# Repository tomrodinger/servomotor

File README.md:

# Gearotons M17 — an open-source servomotor you can talk to

The M17 is a NEMA-17 **integrated servomotor**: motor, closed-loop driver, motion controller and
magnetic encoder in one unit. It daisy-chains over RS-485, ships with Python and Arduino libraries,
and has a first-party [MCP server](https://github.com/Gearotons/servomotor-mcp) so an AI assistant
(Claude Desktop, Claude Code, Cursor, …) can drive real motors from plain English.

Hardware, firmware and software are all in this repository under the MIT license.

| | M17-34 | M17-40 | M17-48 | M17-60 |
|---|---|---|---|---|
| Length | 33.5 mm | 40.1 mm | 48.7 mm | 59.7 mm |
| Holding torque | 0.28 N·m | 0.42 N·m | 0.55 N·m | 0.65 N·m |
| Weight | 210 g | 285 g | 360 g | 470 g |

All sizes: 12–24 V, up to ~1.1 A, up to 560 RPM, closed-loop 32 kHz control, RS-485 at 230400 baud,
64-bit unique ID + one-byte alias per motor, standard NEMA-17 mount. Indoor use (IP20).

**Buy one:** [gearotons.com](https://gearotons.com) (from $20; ships worldwide from Shenzhen).
**Documentation:** [9o.at/M17_1.5](https://9o.at/M17_1.5) ·
[Datasheet (PDF)](servomotor_datasheets/datasheet_latest_en.pdf) ·
[Python API](API_documentation/M17_servomotor_Python_API_documentation.md) ·
[Arduino API](API_documentation/M17_servomotor_Arduino_API_documentation.md)

## Quick start (Python)

```bash
pip install servomotor
```

```python
import time, servomotor

servomotor.open_serial_port()                      # prompts for the USB–RS-485 adapter the first time
m = servomotor.M3("X", time_unit="seconds", position_unit="shaft_rotations")
m.enable_mosfets()
m.trapezoid_move(1.0, 1.0)                         # one full turn, in one second
time.sleep(1.1)
m.disable_mosfets()
servomotor.close_serial_port()
```

That is [`python_programs/example_trapezoid_move.py`](python_programs/example_trapezoid_move.py).
Units are yours to choose (degrees, rotations, radians, encoder counts; seconds or milliseconds) —
the library converts. No STEP/DIR timing, no microstep configuration.

## Quick start (Arduino / ESP32)

Install the **Servomotor** library by Gearotons from the Arduino Library Manager, or from
[`Arduino_library/`](Arduino_library/). Wire the board's UART to an RS-485 transceiver, then:

```cpp
#include <Servomotor.h>

void setup() {
  Servomotor motor('X', Serial1);                  // alias 'X'; the port opens on first use
  motor.setPositionUnit(PositionUnit::SHAFT_ROTATIONS);
  motor.setTimeUnit(TimeUnit::SECONDS);
  motor.enableMosfets();
  motor.trapezoidMove(2.0f, 3.0f);                 // two rotations over three seconds
  delay(4000);
  Serial.println(motor.getPosition());             // commanded position; getHallSensorPosition() reads measured position
}
void loop() {}
```

That is a trimmed [`Arduino_library/example_one_move.cpp`](Arduino_library/example_one_move.cpp)
(the full file adds the ESP32 RS-485 pin definitions).

## Quick start (talk to it)

```bash
uvx --from servomotor-mcp servomotor-mcp        # runs with a simulated motor if no hardware is attached
```

Add it to Claude Desktop or run `claude mcp add gearotons-motor -- uvx --from servomotor-mcp servomotor-mcp`,
then ask: *"Find my motors, then move the one on the bench to 90 degrees and tell me where it ended up."*
Details and the full tool list: [Gearotons/servomotor-mcp](https://github.com/Gearotons/servomotor-mcp).

<p align="center"><a href="https://github.com/Gearotons/servomotor-mcp/releases/download/v0.3.1/M17-claude-code-demo.mp4">▶ 50-second video: the real motor and this session side by side</a> (recorded 2026-09-09 on a bench M17).</p>

## What is in this repository

| Folder | Contents |
|---|---|
| [`firmware/`](firmware/) | Motor firmware (STM32G0), plus [`bootloader_STM32G030/`](bootloader_STM32G030/) and [`bootloader_STM32G031/`](bootloader_STM32G031/) |
| [`PCB/`](PCB/) | Schematics, board layouts and 3D (STEP) models of the controller board |
| [`python_programs/`](python_programs/) | The `servomotor` Python library source, examples, test and characterisation scripts |
| [`Arduino_library/`](Arduino_library/) | The Arduino/ESP32 C++ library and examples |
| [`API_documentation/`](API_documentation/) | Generated Python and Arduino API references (Markdown and PDF) |
| [`servomotor_datasheets/`](servomotor_datasheets/) | Datasheet sources and PDFs (EN, DE, ES, FR, IT, PT), dimension drawings |
| [`production_test_system/`](production_test_system/), [`motor_tests/`](motor_tests/) | How we test motors before they ship |
| [`marketting_page/`](marketting_page/) | Source of the gearotons.com product page |

The command set is data-driven: every firmware command is defined once in
[`motor_commands.json`](python_programs/servomotor/motor_commands.json) and the Python library, the Arduino library and the MCP server are generated
from it, so they always agree.

## Firmware 0.17.0.0

This M17 release adds **Set immediate position target (49)** and
**Set immediate position target and get position (50)**. The second command
returns the latest stored Hall position. Both require an empty motion queue
and enabled closed-loop position control. PID readback (48) remains available.

```python
m.set_immediate_position_target(1000)
measured = m.set_immediate_position_target_and_get_position(2000)
```

Updated bindings are published as [Python 0.13.0](https://pypi.org/project/servomotor/0.13.0/)
and [Arduino 0.11.0](https://github.com/tomrodinger/Servomotor_Arduino_Library/releases/tag/v0.11.0).
See the [client-library release handoff](LIBRARY_RELEASE_HANDOFF.md) for validation,
release receipts and remaining indexing/publishing follow-ups. The release image targets
**M17 hardware 1.5, software compatibility code 3**. Version 0.17.0.0 promotes
the validated 0.17.0.6 implementation; only the development-version byte changes.
See the [release notes](firmware/firmware_releases/servomotor_M17_fw0.17.0.0_scc3_hw1.5.release_notes.txt)
for behavior, client compatibility, upgrade/rollback commands and validation.
The exact stable image passed 35,148+ canary updates with zero communication
errors; see [release-image results](firmware/immediate_target_validation/2026-11-11/release_0.17.0.0/hardware/HARDWARE_RESULTS.txt).
The [firmware release index](firmware/firmware_releases/README.md) lists images,
release notes, checksums and manifests, including the preceding 0.16.0.0 release.

## Immediate targets and ServoTune

Both commands require an empty queue and enabled closed-loop position control.
They retain PID history and protections. Validation runs with interrupts enabled;
only the target/planner stores are masked. Command 50 reads cached Hall position
atomically afterwards, without a sensor recalculation or control-tick wait.
Its reply confirms reference installation, not shaft arrival.

The exact 0.17.0.0 image passed 35,148+ canary updates, both CRC modes,
protection/recovery, native C++ clients and timed-move followups, with zero
communication errors. [Release-image results](firmware/immediate_target_validation/2026-11-11/release_0.17.0.0/hardware/HARDWARE_RESULTS.txt) include timing limits.
Updated Python/Arduino bindings and ServoTune recognize stable 0.17.0.0;
ServoTune also retains the legacy 24-byte reply for development 0.17.0.2.

Try the [ServoTune browser bench](servotune/README.md) without a motor:

```sh
python3 servotune/serve.py
```

The launcher opens a clearly labelled demo with simulated data. The modified
client serializes request/reply transactions and supports both new commands.
The published stable firmware is 0.17.0.0. The preceding 0.16.0.0 release
does not implement immediate-target commands.

## Where the M17 is not the right tool

Direct-drive torque tops out at 0.65 N·m (gear it or go up a frame size for more), it is IP20 and
indoor-only, and it is not a STEP/DIR drop-in for an existing 3D-printer board — it wants a serial
bus and a host that sends it moves. We would rather you know that before you buy.

## Community and support

Questions and builds: [GitHub Discussions](https://github.com/tomrodinger/servomotor/discussions) ·
email [info@gearotons.com](mailto:info@gearotons.com). Issues and pull requests welcome — the whole
stack is here to be read, modified and improved.

Built and assembled by Gearotons in Shenzhen. MIT license — see [LICENSE](LICENSE).

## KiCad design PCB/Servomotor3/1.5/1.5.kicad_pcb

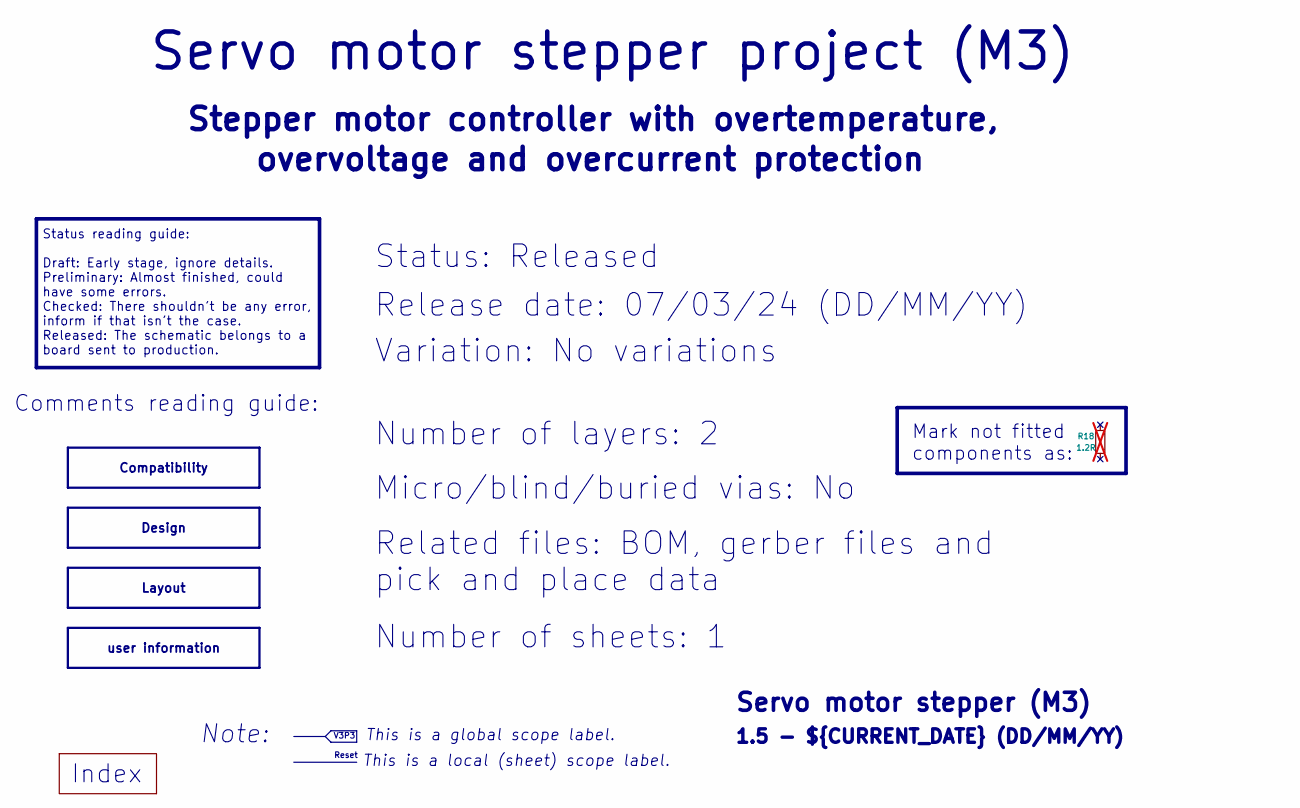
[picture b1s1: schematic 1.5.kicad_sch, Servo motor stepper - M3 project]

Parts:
R18: 1.2R; R_0402_1005Metric; not fitted

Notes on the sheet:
Variation: No variations
${REVISION} - ${CURRENT_DATE} (DD/MM/YY)
Status reading guide: Draft: Early stage, ignore details. Preliminary: Almost finished, could have some errors. Checked: There shouldn't be any error, inform if that isn't the case. Released: The schematic belongs to a board sent to production.
Servo motor stepper project (M3)
This is a global scope label.
Micro/blind/buried vias: No
Status: Released
Comments reading guide:
overvoltage and overcurrent protection
Reset
Note:
Stepper motor controller with overtemperature,
Related files: BOM, gerber files and pick and place data
Number of sheets: 1
This is a local (sheet) scope label.
Index
Mark not fitted components as:
Number of layers: 2
Release date: 07/03/24 (DD/MM/YY)
V3P3
Servo motor stepper (M3)
Design
user information
Compatibility
Layout

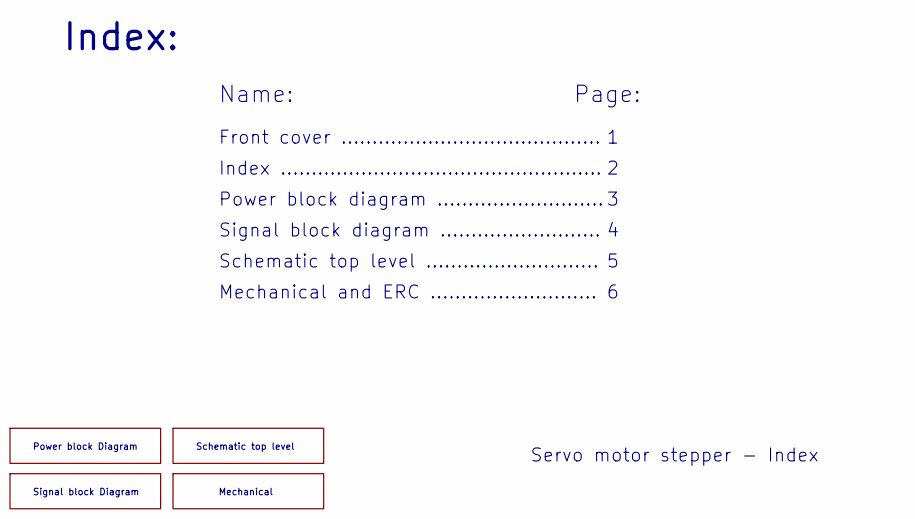
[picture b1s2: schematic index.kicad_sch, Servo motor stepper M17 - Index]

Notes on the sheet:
Power block Diagram
Front cover ..........................................
Mechanical
Schematic top level
Schematic top level ............................
Index ....................................................
Signal block diagram ..........................
Signal block Diagram
Name:
Mechanical and ERC ...........................
Page:
Servo motor stepper - Index
Power block diagram ...........................
Index:

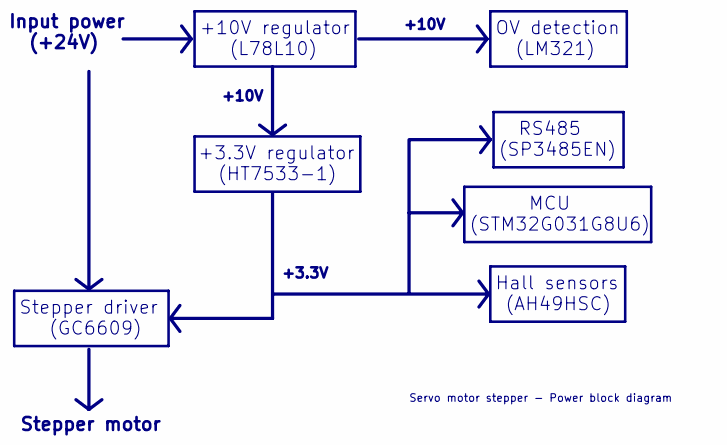
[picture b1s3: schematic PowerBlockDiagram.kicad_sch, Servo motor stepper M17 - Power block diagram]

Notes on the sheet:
+3.3V
Stepper driver (GC6609)
+10V
RS485 (SP3485EN)
Hall sensors (AH49HSC)
Servo motor stepper - Power block diagram
+3.3V regulator (HT7533-1)
+10V regulator (L78L10)
OV detection (LM321)
Input power (+24V)
Stepper motor
MCU (STM32G031G8U6)

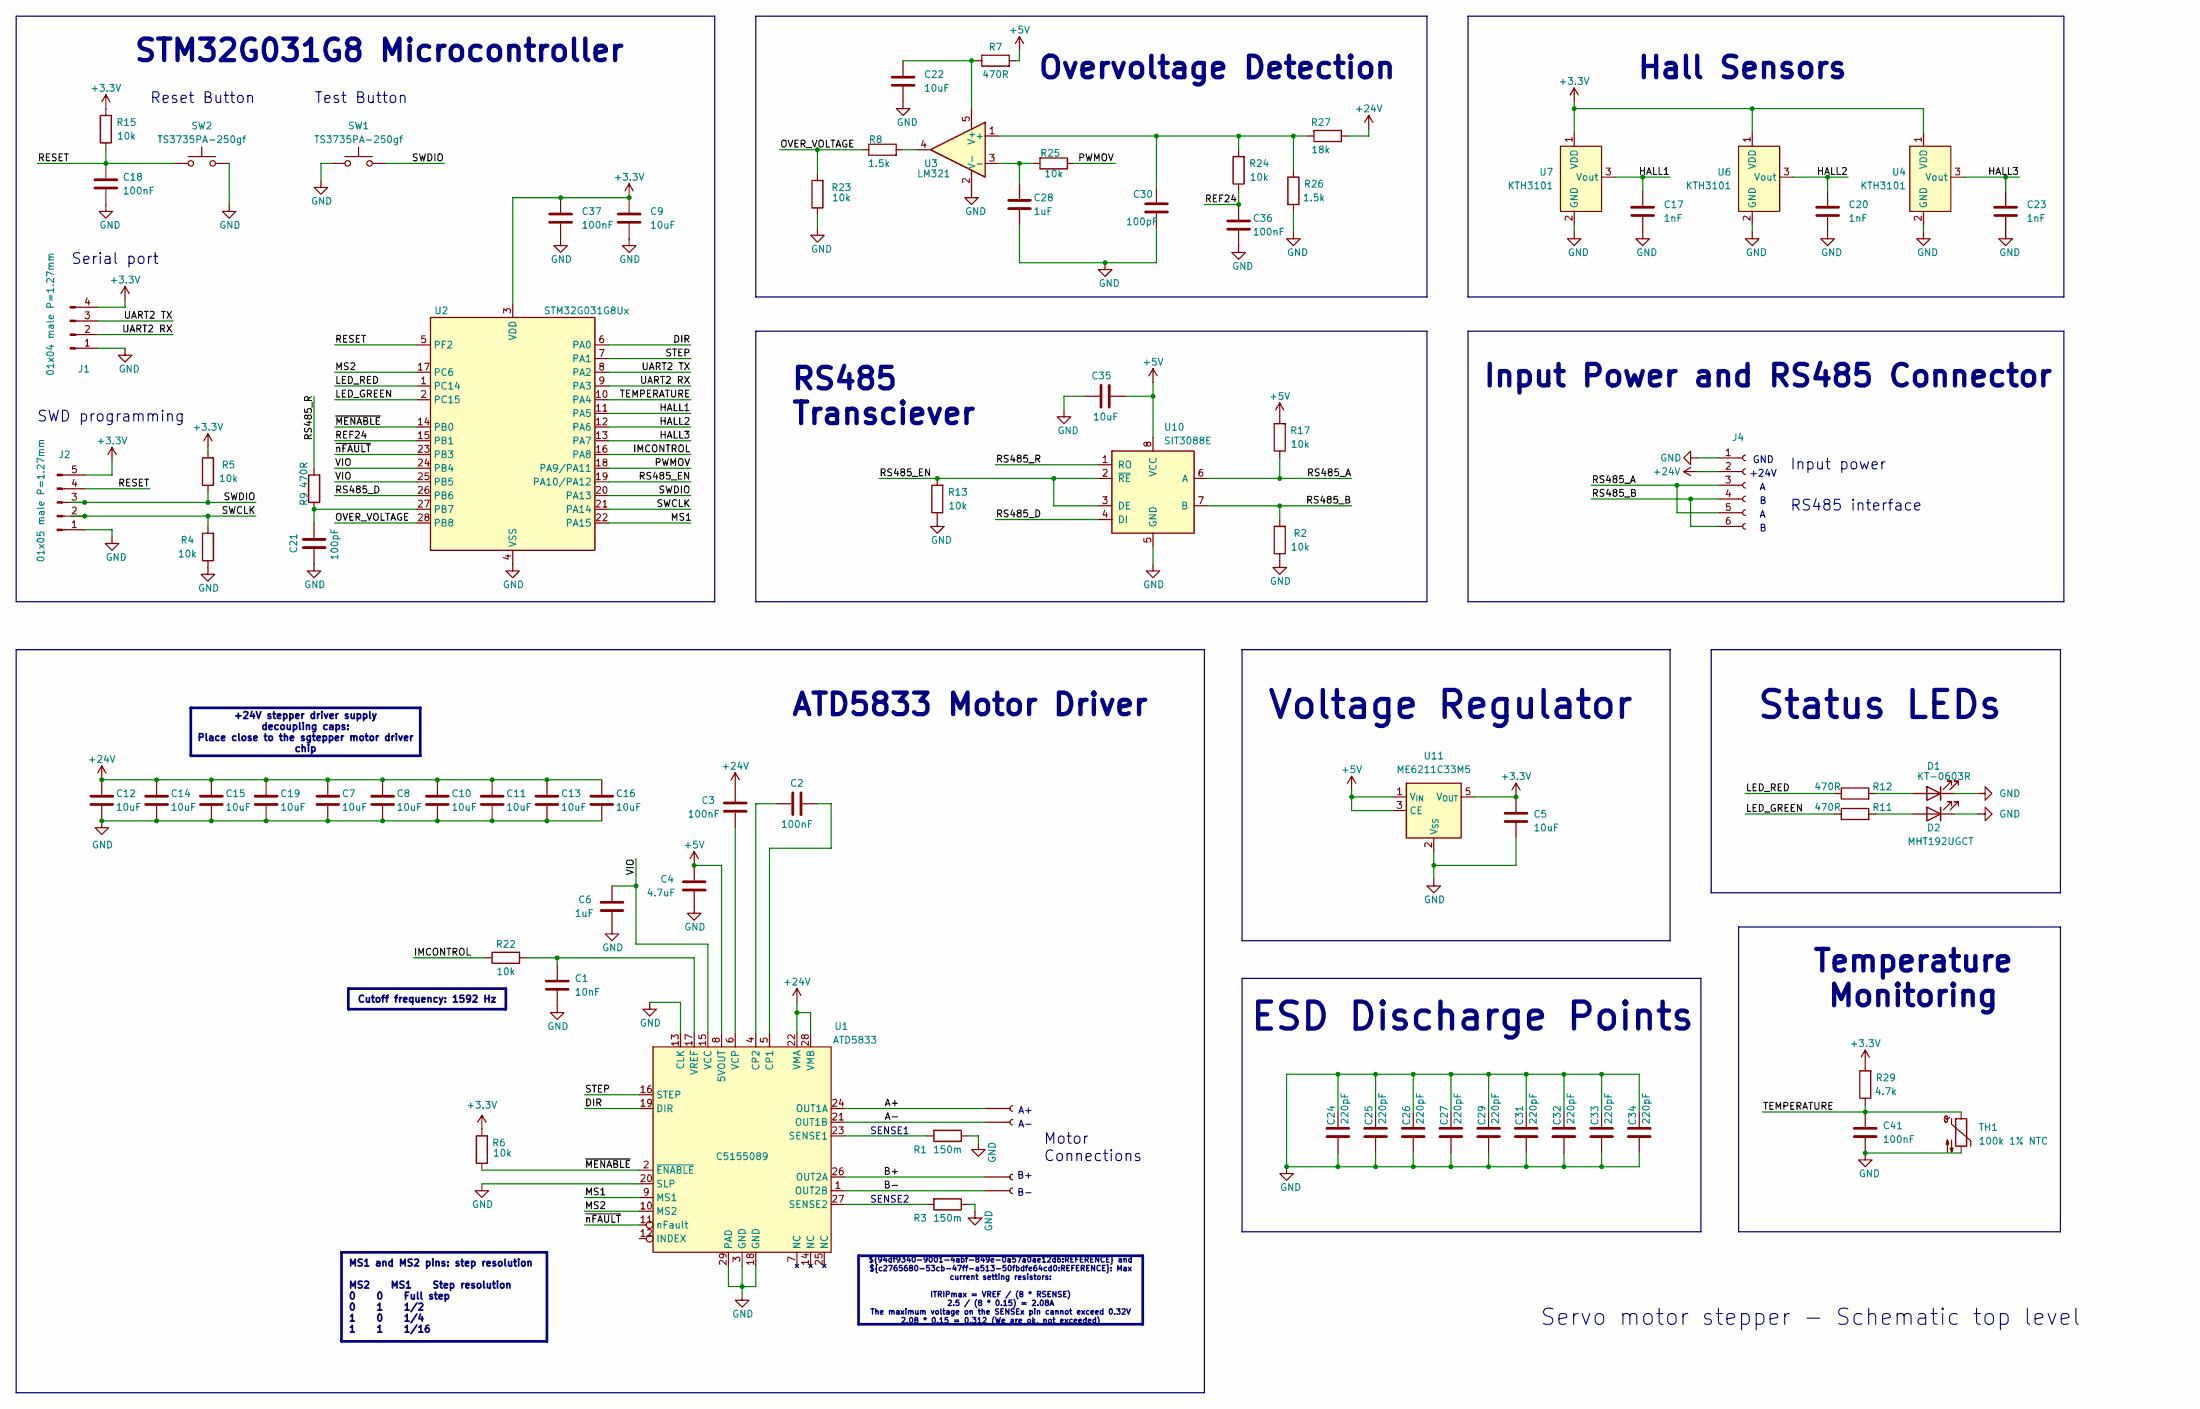
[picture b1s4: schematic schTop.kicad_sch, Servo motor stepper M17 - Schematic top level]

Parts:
C1: 10nF; C_0402_1005Metric; LCSC C15195
C2, C3, C18, C36, C37, C41: 100nF; C_0402_1005Metric; LCSC C307331
C4: 4.7uF; C_0402_1005Metric; LCSC C23733
C5, C9, C22, C35: 10uF; C_0402_1005Metric; LCSC C15525
C6, C28: 1uF; C_0402_1005Metric; LCSC C52923
C7, C8, C10, C11, C12, C13, C14, C15, C16, C19: 10uF; C_0603_1608Metric; LCSC C194427
C17, C20, C23: 1nF; C_0402_1005Metric; LCSC C1523
C21, C30: 100pF; C_0402_1005Metric; LCSC C1546
C24, C25, C26, C27, C29, C31, C32, C33, C34: 220pF; C_0402_1005Metric; LCSC C1530
D1: KT-0603R; LED_0603_1608Metric; LCSC C2286
D2: MHT192UGCT; LED_0603_1608Metric; LCSC C389519
J1: 01x04 male P=1.27mm; PinHeader_1x04_P1.27mm_Vertical_No_Silkprint
J2: 01x05 male P=1.27mm; PinHeader_1x05_P1.27mm_Vertical_No_Silkprint
J3, J5, J6, J7: Conn_01x01_Socket; Pad_3mm_TopOnly
J4: Conn_01x06_Socket; PinSocket_1x06_P2.00mm_Vertical
R1, R3: 150m; R_2010_5025Metric; LCSC C474275
R2, R4, R5, R6, R13, R15, R17, R22, R23, R24, R25: 10k; R_0402_1005Metric; LCSC C25744
R7, R9, R11, R12: 470R; R_0402_1005Metric; LCSC C25117
R8, R26: 1.5k; R_0402_1005Metric; LCSC C25867
R27: 18k; R_0603_1608Metric; LCSC C25810
R29: 4.7k; R_0402_1005Metric; LCSC C25900
SW1, SW2: TS3735PA-250gf; LCSC C393946
TH1: 100k 1% NTC; R_0402_1005Metric; LCSC C236279
U1: ATD5833; QFN-28-1EP_5x5mm_P0.5mm_EP3.75x3.75mm_ThermalVias; LCSC C5155089
U2: STM32G031G8Ux; QFN-28_4x4mm_P0.5mm; LCSC C432211
U3: LM321; SOT-23-5; LCSC C19723728
U4, U6, U7: KTH3101; DFN1616; LCSC C49258056
U10: SIT3088E; DFN-8-1EP_3x3mm_P0.65mm_EP1.5x2.25mm; LCSC C601076
U11: ME6211C33M5; SOT-23-5; LCSC C82942

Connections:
+3.3V: C5.1, C9.1, C37.1, J1.4, J2.5, R5.2, R6.2, R15.2, R29.2, U2.3 (VDD), U4.1 (VDD), U6.1 (VDD), U7.1 (VDD), U11.5 (V_{OUT})
+5V: C4.1, C35.2, R7.2, R17.2, U1.8 (5VOUT), U10.8 (VCC), U11.1 (V_{IN}), U11.3 (CE)
+24V: C3.1, C7.1, C8.1, C10.1, C11.1, C12.1, C13.1, C14.1, C15.1, C16.1, C19.1, J4.2, R27.1, U1.22 (VMA), U1.28 (VMB)
/index/schTop/A+: J3.1, U1.24 (OUT1A)
/index/schTop/A-: J6.1, U1.21 (OUT1B)
/index/schTop/B+: J7.1, U1.26 (OUT2A)
/index/schTop/B-: J5.1, U1.1 (OUT2B)
/index/schTop/DIR: U1.19 (DIR), U2.6 (PA0)
/index/schTop/HALL1: C17.1, U2.11 (PA5), U7.3 (Vout)
/index/schTop/HALL2: C20.1, U2.12 (PA6), U6.3 (Vout)
/index/schTop/HALL3: C23.1, U2.13 (PA7), U4.3 (Vout)
/index/schTop/IMCONTROL: R22.1, U2.16 (PA8)
/index/schTop/LED_GREEN: R11.1, U2.2 (PC15)
/index/schTop/LED_RED: R12.1, U2.1 (PC14)
/index/schTop/MS1: U1.9 (MS1), U2.22 (PA15)
/index/schTop/MS2: U1.10 (MS2), U2.17 (PC6)
/index/schTop/OVER_VOLTAGE: R8.1, R23.2, U2.28 (PB8)
/index/schTop/PWMOV: R25.1, U2.18 (PA9/PA11)
/index/schTop/REF24: C36.1, R24.1, U2.15 (PB1)
/index/schTop/RESET: C18.1, J2.4, R15.1, SW2.1, U2.5 (PF2)
/index/schTop/RS485_A: J4.3, J4.5, R17.1, U10.6 (A)
/index/schTop/RS485_B: J4.4, J4.6, R2.2, U10.7 (B)
/index/schTop/RS485_D: U2.26 (PB6), U10.4 (DI)
/index/schTop/RS485_EN: R13.2, U2.19 (PA10/PA12), U10.2 (~RE), U10.3 (DE)
/index/schTop/RS485_R: R9.2, U10.1 (RO)
/index/schTop/STEP: U1.16 (STEP), U2.7 (PA1)
/index/schTop/SWCLK: J2.2, R4.2, U2.21 (PA14)
/index/schTop/SWDIO: J2.3, R5.1, SW1.2, U2.20 (PA13)
/index/schTop/TEMPERATURE: C41.1, R29.1, TH1.1, U2.10 (PA4)
/index/schTop/UART2 RX: J1.2, U2.9 (PA3)
/index/schTop/UART2 TX: J1.3, U2.8 (PA2)
/index/schTop/VIO: C6.1, U1.15 (VCC), U2.24 (PB4), U2.25 (PB5)
/index/schTop/~MENABLE: R6.1, U1.2 (~ENABLE), U2.14 (PB0)
/index/schTop/~nFAULT: U1.11 (nFault), U2.23 (PB3)
GND: C1.2, C4.2, C5.2, C6.2, C7.2, C8.2, C9.2, C10.2, C11.2, C12.2, C13.2, C14.2, C15.2, C16.2, C17.2, C18.2, C19.2, C20.2, C21.2, C22.2, C23.2, C24.1, C24.2, C25.1, C25.2, C26.1, C26.2, C27.1, C27.2, C28.2, C29.1, C29.2, C30.2, C31.1, C31.2, C32.1, C32.2, C33.1, C33.2, C34.1, C34.2, C35.1, C36.2, C37.2, C41.2, D1.1 (K), D2.1 (K), J1.1, J2.1, J4.1, R1.1, R2.1, R3.1, R4.1, R13.1, R23.1, R26.2, SW1.1, SW2.2, TH1.2, U1.3 (GND), U1.13 (CLK), U1.18 (GND), U1.20 (SLP), U1.29 (PAD), U2.4 (VSS), U3.2 (V-), U4.2 (GND), U6.2 (GND), U7.2 (GND), U10.5 (GND), U11.2 (V_{SS})
unnamed: D1.2 (A), R12.2
unnamed: D2.2 (A), R11.2
unnamed: R8.2, U3.4
unnamed: C2.2, U1.5 (CP1)
unnamed: C2.1, U1.4 (CP2)
unnamed: R1.2, U1.23 (SENSE1)
unnamed: R3.2, U1.27 (SENSE2)
unnamed: C3.2, U1.6 (VCP)
unnamed: C1.1, R22.2, U1.17 (VREF)
unnamed: C21.1, R9.1, U2.27 (PB7)
unnamed: C30.1, R24.2, R26.1, R27.2, U3.1 (+)
unnamed: C28.1, R25.2, U3.3 (-)
unnamed: C22.1, R7.1, U3.5 (V+)

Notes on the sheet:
Reset Button
ESD Discharge Points
Test Button
+24V
SWD programming
Serial port
GND
RS485 Transciever
Input power
Status LEDs
Overvoltage Detection
Voltage Regulator
Input Power and RS485 Connector
SENSE2
RS485 interface
Temperature Monitoring
SENSE1
Servo motor stepper - Schematic top level
STM32G031G8 Microcontroller
ATD5833 Motor Driver
Hall Sensors
Motor Connections
Cutoff frequency: 1592 Hz
+24V stepper driver supply decoupling caps: Place close to the sgtepper motor driver chip
MS1 and MS2 pins: step resolution MS2 MS1 Step resolution 0 0 Full step 0 1 1/2 1 0 1/4 1 1 1/16
${94df9340-9001-4abf-849e-0a57a0ae12d6:REFERENCE} and ${c2765680-53cb-47ff-a513-50fbdfe64cd0:REFERENCE}: Max current setting resistors: ITRIPmax = VREF / (8 * RSENSE) 2.5 / (8 * 0.15) = 2.08A The maximum voltage on the SENSEx pin cannot exceed 0.32V 2.08 * 0.15 = 0.312 (We are ok, not exceeded)

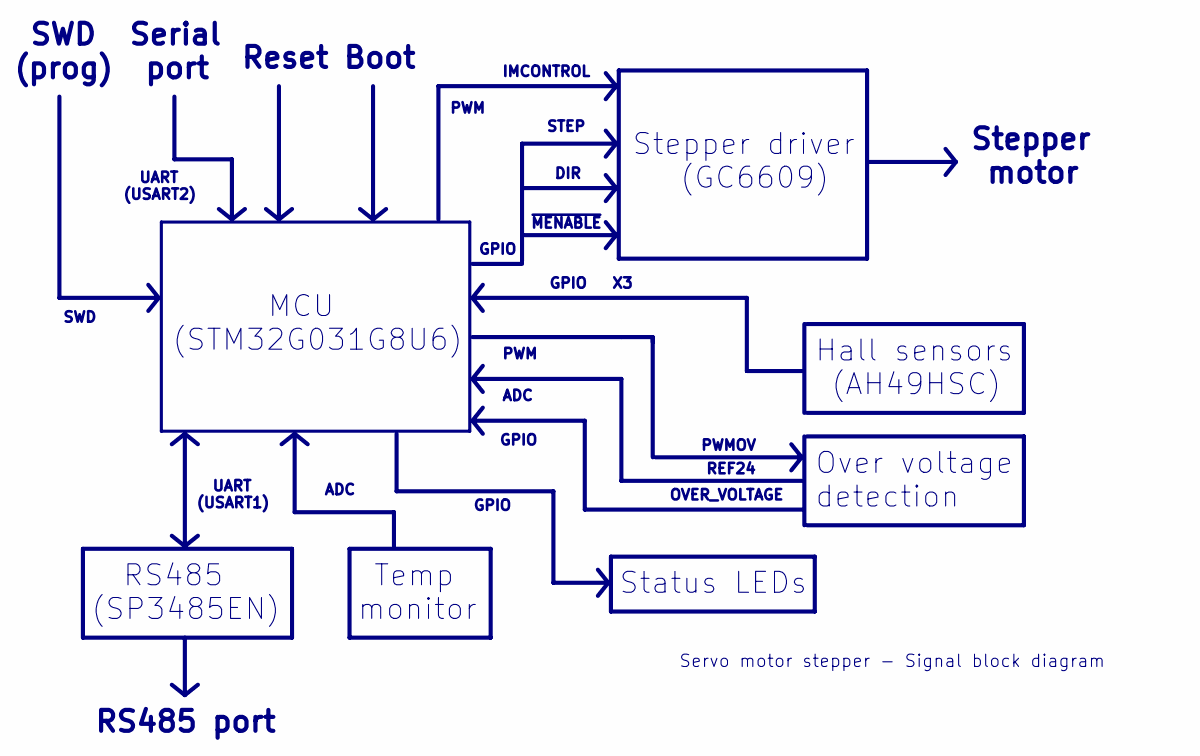
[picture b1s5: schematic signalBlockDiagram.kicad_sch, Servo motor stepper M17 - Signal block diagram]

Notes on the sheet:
~{MENABLE}
Stepper driver (GC6609)
Serial port
REF24
RS485 (SP3485EN)
Temp monitor
UART (USART2)
MCU (STM32G031G8U6)
IMCONTROL
ADC
UART (USART1)
PWM
GPIO
STEP
SWD (prog)
Over voltage detection
OVER_VOLTAGE
Status LEDs
Boot
PWMOV
Reset
DIR
Stepper motor
RS485 port
Servo motor stepper - Signal block diagram
Hall sensors (AH49HSC)
SWD

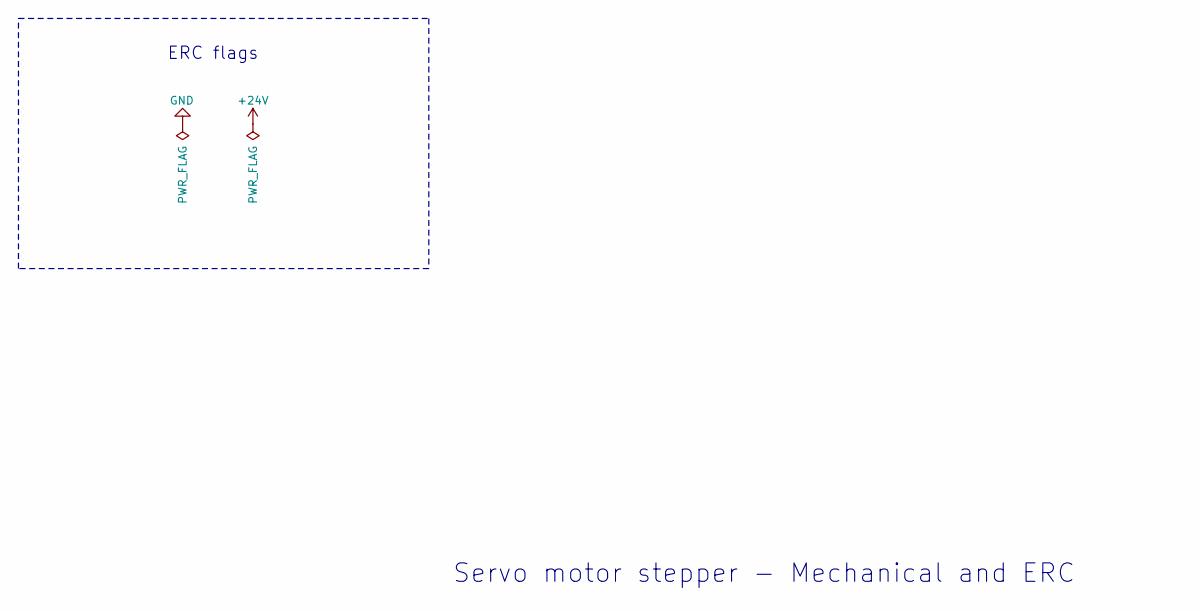
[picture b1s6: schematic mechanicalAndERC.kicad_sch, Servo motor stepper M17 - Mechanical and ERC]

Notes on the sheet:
ERC flags
Servo motor stepper - Mechanical and ERC

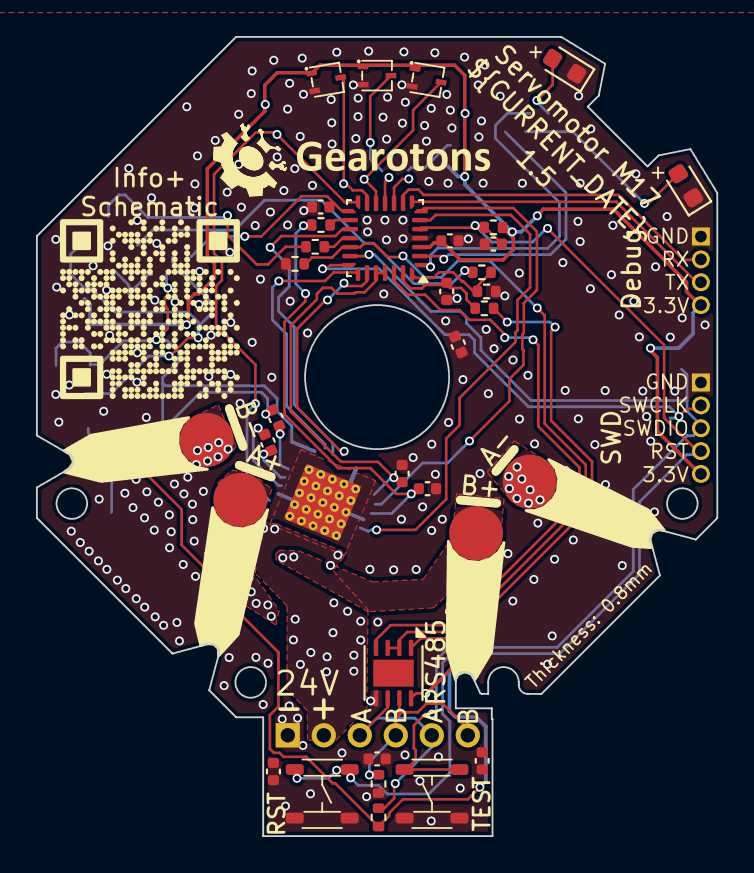
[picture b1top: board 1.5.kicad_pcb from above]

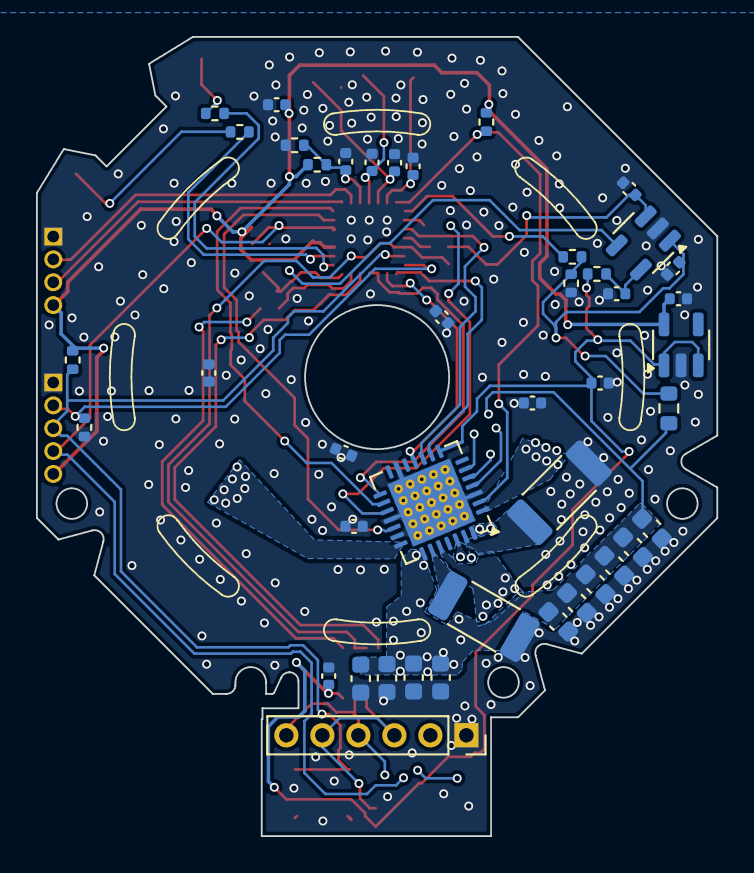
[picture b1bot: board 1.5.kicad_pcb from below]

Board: 2 copper layers, 37.8 x 44.4 mm, 79 parts (43 on the bottom side), 48 nets.

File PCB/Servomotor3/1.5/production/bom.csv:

Designator,Footprint,Quantity,Value,LCSC Part #
C1,0402,1,10nF,C15195
"C10, C11, C12, C13, C14, C15, C16, C19, C7, C8",0603,10,10uF,C194427
"C17, C20, C23",0402,3,1nF,C1523
"C18, C2, C3, C36, C37, C41",0402,6,100nF,C307331
"C21, C30",0402,2,100pF,C1546
"C22, C35, C5, C9",0402,4,10uF,C15525
"C24, C25, C26, C27, C29, C31, C32, C33, C34",0402,9,220pF,C1530
"C28, C6",0402,2,1uF,C52923
C4,0402,1,4.7uF,C23733
D1,0603,1,KT-0603R,C2286
D2,0603,1,MHT192UGCT,C389519
J4,PinSocket_1x06_P2.00mm_Vertical,1,Conn_01x06_Socket,
"R1, R3",2010,2,150m,C474275
"R11, R12, R7, R9",0402,4,470R,C25117
"R13, R15, R17, R2, R22, R23, R24, R25, R4, R5, R6",0402,11,10k,C25744
"R26, R8",0402,2,1.5k,C25867
R27,0603,1,18k,C25810
R29,0402,1,4.7k,C25900
"SW1, SW2",TS3735PA-250gf,2,TS3735PA-250gf,C393946
TH1,0402,1,100k 1% NTC,C236279
U1,QFN-28-1EP_5x5mm_P0.5mm_EP3.75x3.75mm_ThermalVias,1,ATD5833,C5155089
U10,DFN-8-1EP_3x3mm_P0.65mm_EP1.5x2.25mm,1,SIT3088E,C601076
U11,SOT-23-5,1,ME6211C33M5,C82942
U2,QFN-28_4x4mm_P0.5mm,1,STM32G031G8Ux,C432211
U3,SOT-23-5,1,LM321,C19723728
"U4, U6, U7",DFN1616,3,KTH3101,C49258056

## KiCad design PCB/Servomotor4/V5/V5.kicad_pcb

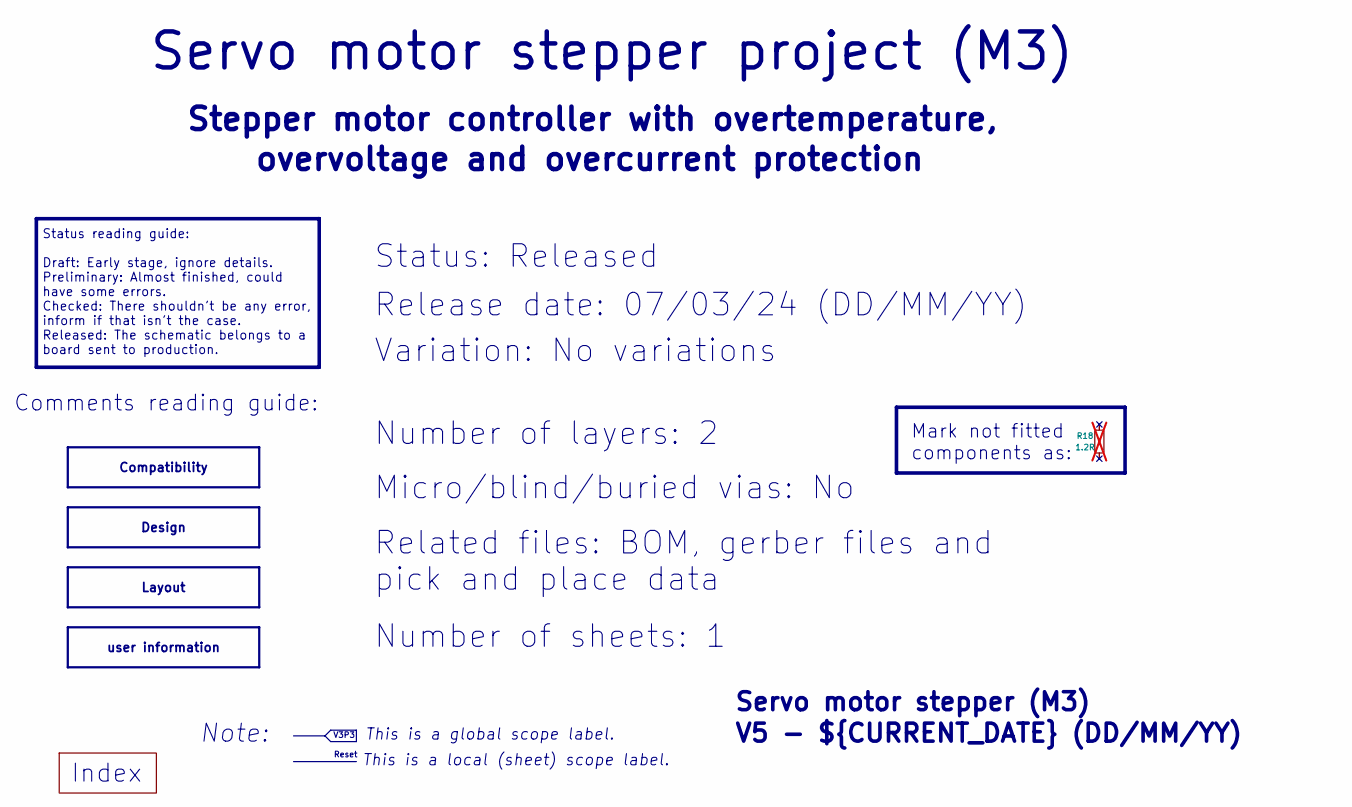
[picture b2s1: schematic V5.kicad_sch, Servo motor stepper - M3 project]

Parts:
R18: 1.2R; R_0402_1005Metric; not fitted

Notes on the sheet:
Design
user information
Compatibility
Layout
Variation: No variations
${REVISION} - ${CURRENT_DATE} (DD/MM/YY)
Status reading guide: Draft: Early stage, ignore details. Preliminary: Almost finished, could have some errors. Checked: There shouldn't be any error, inform if that isn't the case. Released: The schematic belongs to a board sent to production.
Servo motor stepper project (M3)
This is a global scope label.
Micro/blind/buried vias: No
Status: Released
Comments reading guide:
overvoltage and overcurrent protection
Reset
Note:
Stepper motor controller with overtemperature,
Related files: BOM, gerber files and pick and place data
Number of sheets: 1
This is a local (sheet) scope label.
Index
Mark not fitted components as:
Number of layers: 2
Release date: 07/03/24 (DD/MM/YY)
V3P3
Servo motor stepper (M3)

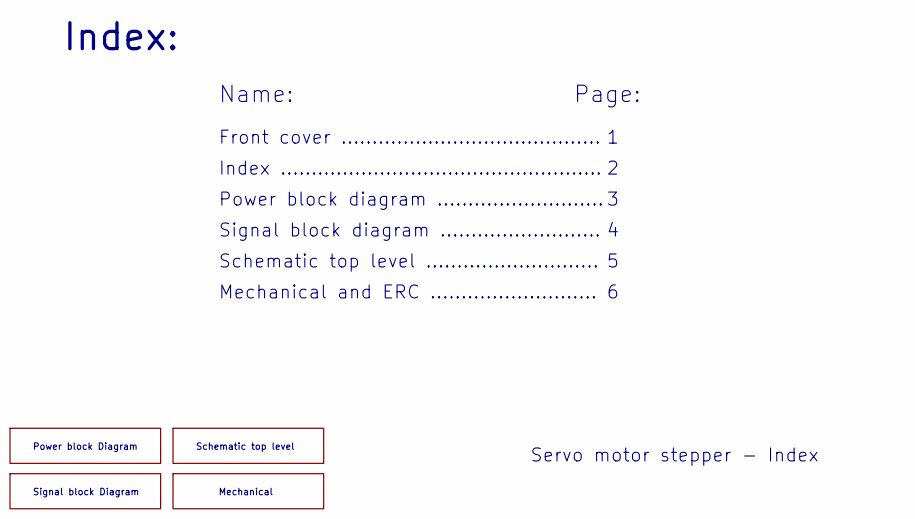
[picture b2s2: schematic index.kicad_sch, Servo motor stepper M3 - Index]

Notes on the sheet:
Power block Diagram
Front cover ..........................................
Mechanical
Schematic top level
Schematic top level ............................
Index ....................................................
Signal block diagram ..........................
Signal block Diagram
Name:
Mechanical and ERC ...........................
Page:
Servo motor stepper - Index
Power block diagram ...........................
Index:

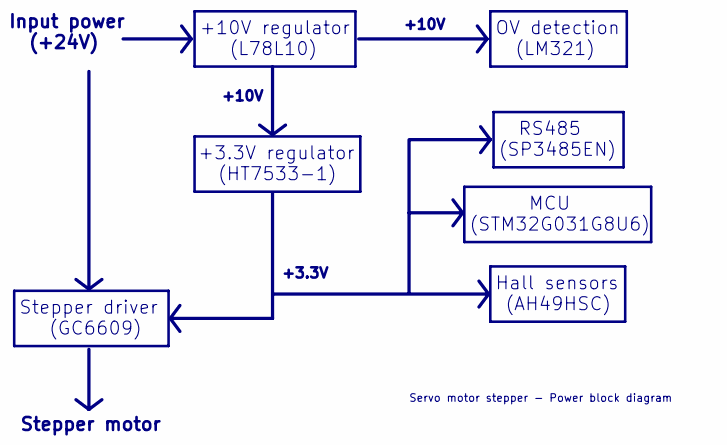
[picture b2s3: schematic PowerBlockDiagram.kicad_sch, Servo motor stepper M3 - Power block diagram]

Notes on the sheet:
+3.3V
Stepper driver (GC6609)
+10V
RS485 (SP3485EN)
Hall sensors (AH49HSC)
Servo motor stepper - Power block diagram
+3.3V regulator (HT7533-1)
+10V regulator (L78L10)
OV detection (LM321)
Input power (+24V)
Stepper motor
MCU (STM32G031G8U6)
